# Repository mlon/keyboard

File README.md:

# Keyboard

A custom 37 keys MIDI keyboard

- [case](./case/) contains a step file of the keyboard assembly, and exports of each panel to be cut and bent.
- [pcb](./pcb/) contains the Kicad project for the matrix scanner.
- [src](./src/) contains the firmware for the matrix scanner.

## License

Code: MIT License

Hardware: cc-by-sa-4.0

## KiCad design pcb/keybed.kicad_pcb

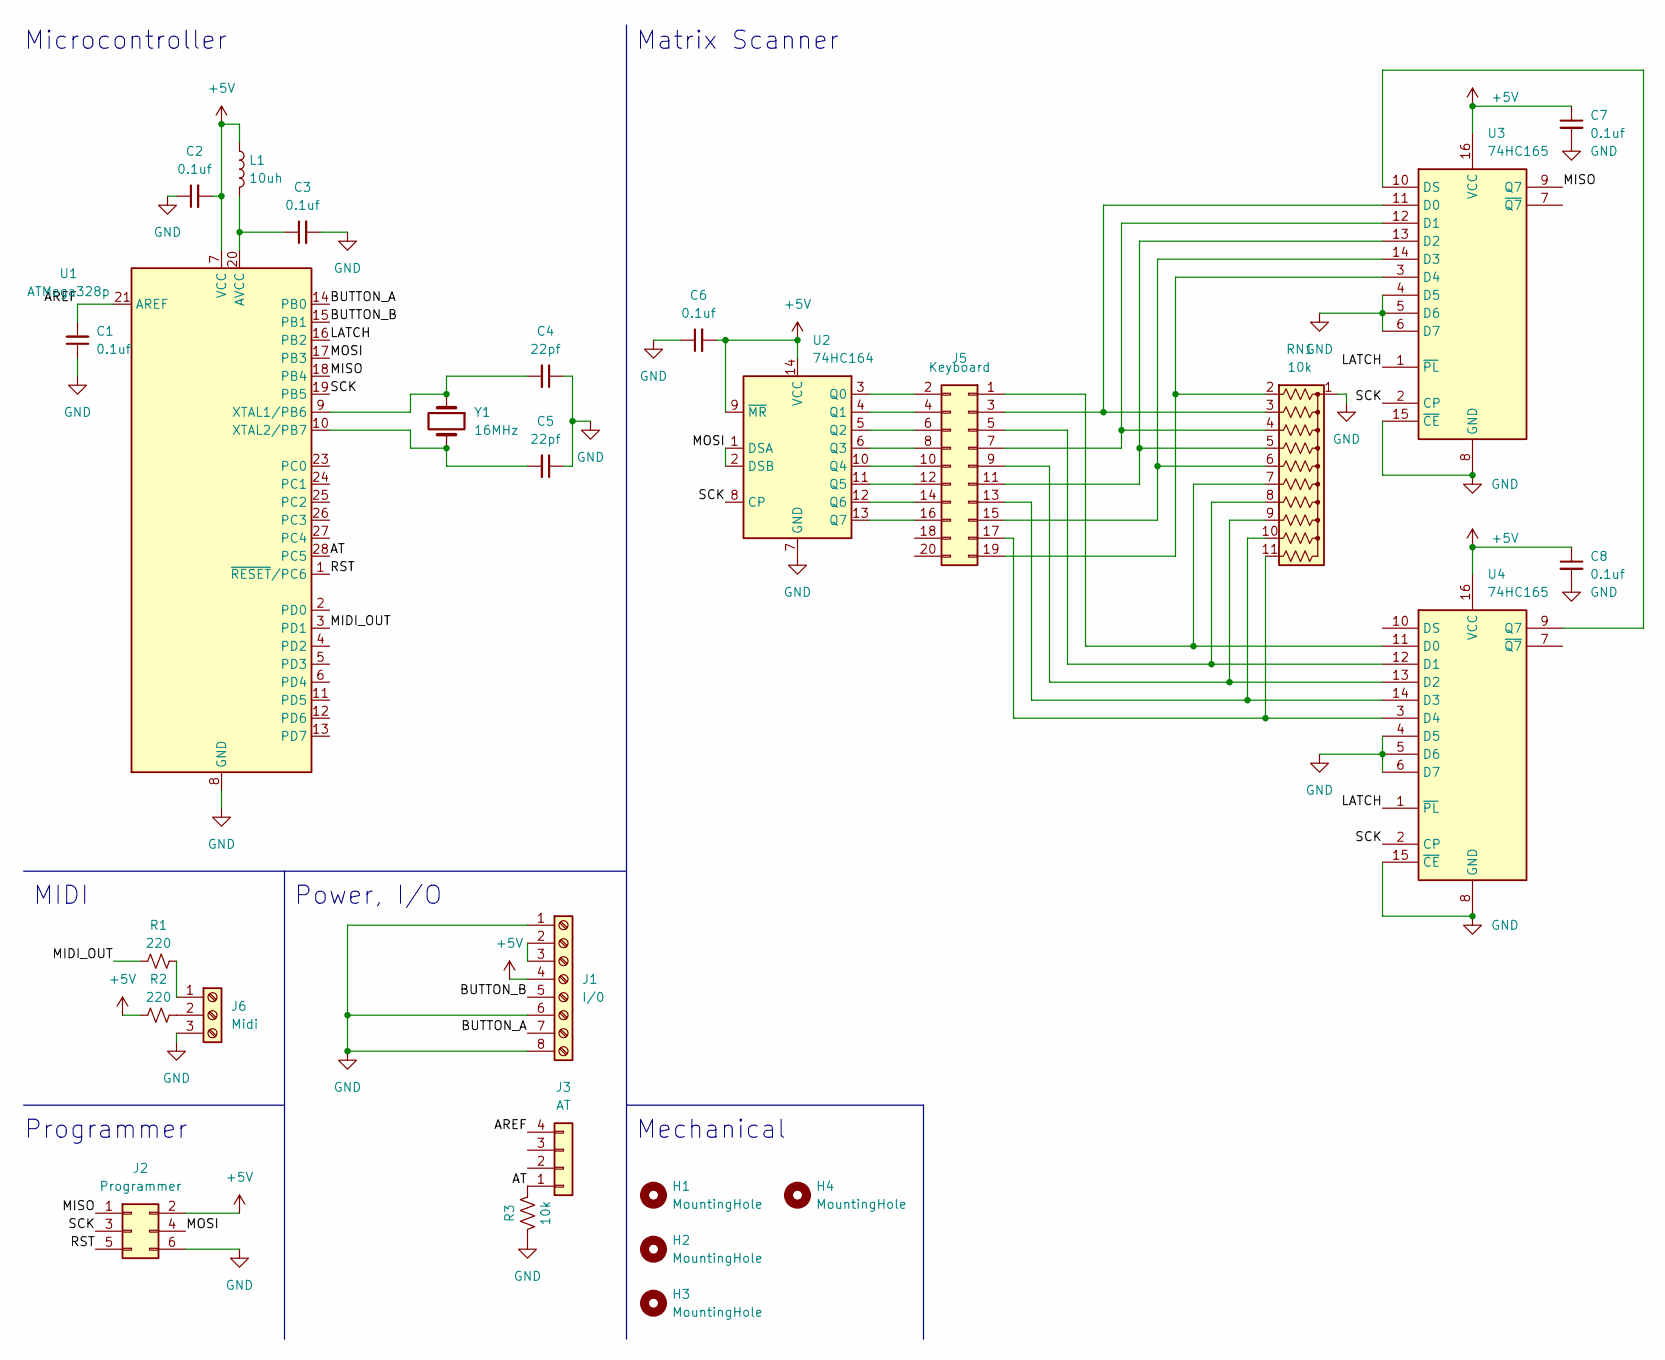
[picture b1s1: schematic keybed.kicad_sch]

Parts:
C1, C2, C3, C6, C7, C8: 0.1uf; C_Disc_D5.0mm_W2.5mm_P2.50mm
C4, C5: 22pf; C_Disc_D5.0mm_W2.5mm_P2.50mm
H1, H2, H3, H4: MountingHole; MountingHole_3.2mm_M3
J1: I/0; Altech_AK300_1x08_P5.00mm_45-Degree
J2: Programmer; PinHeader_2x03_P2.54mm_Vertical
J3: AT; PinHeader_1x04_P2.54mm_Horizontal
J5: Keyboard; TE_9-215079-0
J6: Midi; Altech_AK300_1x03_P5.00mm_45-Degree
L1: 10uh; 22R103C
R1, R2: 220; R_Axial_DIN0207_L6.3mm_D2.5mm_P7.62mm_Horizontal
R3: 10k; R_Axial_DIN0207_L6.3mm_D2.5mm_P7.62mm_Horizontal
RN1: 10k; R_Array_SIP11
U1: ATMega328p; DIP-28_W7.62mm_Socket
U2: 74HC164; DIP-14_W7.62mm_Socket
U3, U4: 74HC165; DIP-16_W7.62mm_Socket
Y1: 16MHz; Crystal_HC49-4H_Vertical

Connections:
+5V: C2.2, C6.2, C7.1, C8.1, J1.4, J2.2, L1.1, R2.1, U1.7 (VCC), U2.9 (~MR), U2.14 (VCC), U3.16 (VCC), U4.16 (VCC)
/AREF: C1.2, J3.4, U1.21 (AREF)
/AT: J3.1, R3.1, U1.28 (PC5)
/BUTTON_A: J1.7, U1.14 (PB0)
/BUTTON_B: J1.5, U1.15 (PB1)
/LATCH: U1.16 (PB2), U3.1 (~PL), U4.1 (~PL)
/MIDI_OUT: R1.1, U1.3 (PD1)
/MISO: J2.1, U1.18 (PB4), U3.9 (Q7)
/MOSI: J2.4, U1.17 (PB3), U2.1 (DSA), U2.2 (DSB)
/RST: J2.5, U1.1 (~RESET/PC6)
/SCK: J2.3, U1.19 (PB5), U2.8 (CP), U3.2 (CP), U4.2 (CP)
GND: C1.1, C2.1, C3.2, C4.1, C5.1, C6.1, C7.2, C8.2, J1.1, J1.6, J1.8, J2.6, J6.3, R3.2, RN1.1 (common), U1.8 (GND), U1.22 (GND), U2.7 (GND), U3.4 (D5), U3.5 (D6), U3.6 (D7), U3.8 (GND), U3.15 (~CE), U4.4 (D5), U4.5 (D6), U4.6 (D7), U4.8 (GND), U4.15 (~CE)
unnamed: C3.1, L1.2, U1.20 (AVCC)
unnamed: C4.2, U1.9 (XTAL1/PB6), Y1.1
unnamed: C5.2, U1.10 (XTAL2/PB7), Y1.2
unnamed: J1.2, J1.3
unnamed: J5.1, RN1.7 (R6), U4.11 (D0)
unnamed: J5.2, U2.3 (Q0)
unnamed: J5.3, RN1.3 (R2), U3.11 (D0)
unnamed: J5.4, U2.4 (Q1)
unnamed: J5.5, RN1.8 (R7), U4.12 (D1)
unnamed: J5.6, U2.5 (Q2)
unnamed: J5.7, RN1.4 (R3), U3.12 (D1)
unnamed: J5.8, U2.6 (Q3)
unnamed: J5.9, RN1.9 (R8), U4.13 (D2)
unnamed: J5.10, U2.10 (Q4)
unnamed: J5.11, RN1.5 (R4), U3.13 (D2)
unnamed: J5.12, U2.11 (Q5)
unnamed: J5.13, RN1.10 (R9), U4.14 (D3)
unnamed: J5.14, U2.12 (Q6)
unnamed: J5.15, RN1.6 (R5), U3.14 (D3)
unnamed: J5.16, U2.13 (Q7)
unnamed: J5.17, RN1.11 (R10), U4.3 (D4)
unnamed: J5.19, RN1.2 (R1), U3.3 (D4)
unnamed: J6.1, R1.2
unnamed: J6.2, R2.2
unnamed: U3.10 (DS), U4.9 (Q7)

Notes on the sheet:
Mechanical
Matrix Scanner
Microcontroller
Power, I/O
Programmer
MIDI

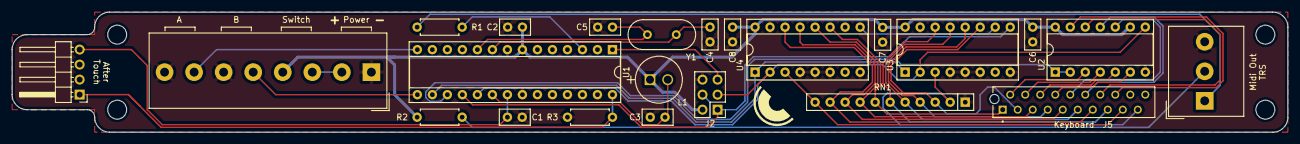
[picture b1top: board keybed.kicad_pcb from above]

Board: 2 copper layers, 215.9 x 20.3 mm, 27 parts (0 on the bottom side), 37 nets.

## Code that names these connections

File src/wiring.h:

#pragma once

// PortB
#define BUTTON_A 0
#define BUTTON_B 1
#define LATCH 2
#define MOSI 3
#define MISO 4
#define SCK 5

// PortC
#define AFTER_TOUCH 5

// PortD
#define TX 1

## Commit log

2022-03-13 Matrix Scanning
2022-04-23 Build/debug boilerplate for atmegap328p
2022-05-07 More setup and testing
2022-06-19 Checkpoint
2022-06-22 Stubbing out matrix scanning
2022-09-01 Stash
2022-09-01 More modularization
2022-09-02 Use SPI for matrix scanning
2022-09-04 Working matrix scan and velocity
2022-09-05 Make velocity work
2022-10-17 Add support for transpose buttons
2022-10-17 Added schematic and files to build case
2022-10-17 added visuals

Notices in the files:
parts and their libraries:
Copyright 2021 Accelerated Designs. All rights reserved.
